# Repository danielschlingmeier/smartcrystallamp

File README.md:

# smartcrystallamp
Smart Crystal Lamp Project

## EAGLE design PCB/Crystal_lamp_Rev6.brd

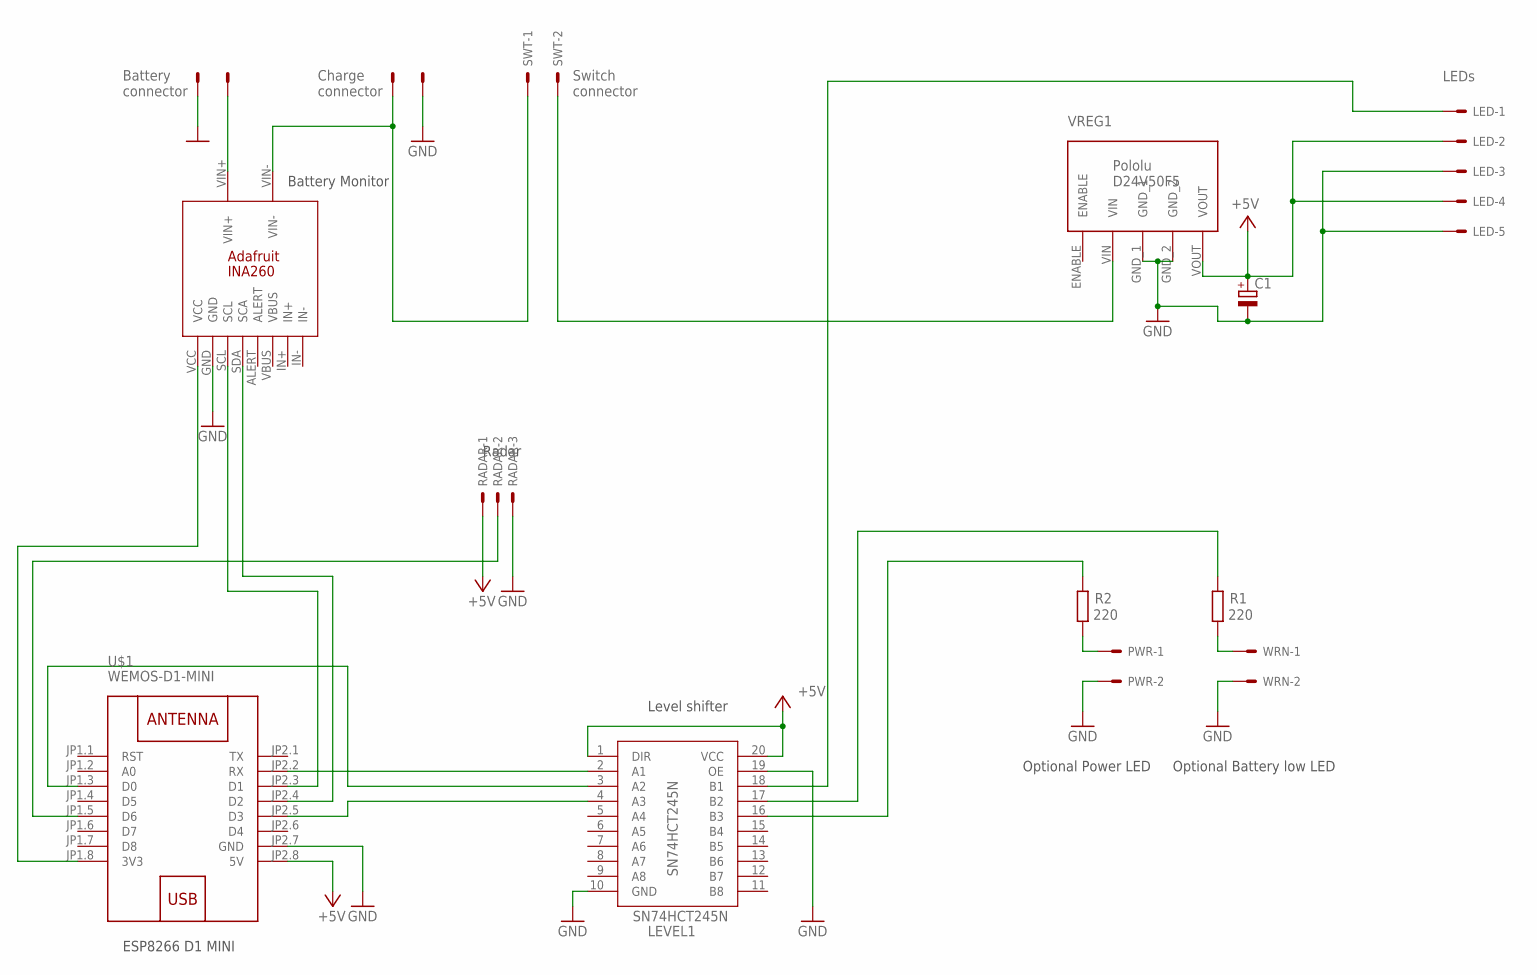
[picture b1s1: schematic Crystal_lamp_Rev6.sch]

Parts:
BAT: 22-27-2021-02; 6410-02
C1: CPOL-EUE5-10.5; E5-10,5
CRG: 22-27-2021-02; 6410-02
INA1: INA260
LED: 22-27-2051-05; 6410-05
LEVEL1: SN74HCT245N; DIL20
PWR: 22-27-2021-02; 6410-02
R1, R2: 220; 0207/10
RADAR: 22-27-2031-03; 6410-03
SWT: 22-27-2021-02; 6410-02
U$1: WEMOS-D1-MINI
VREG1: D24V50F5
WRN: 22-27-2021-02; 6410-02

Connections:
+5V: C1.+, LED.2, LED.4, LEVEL1.1 (DIR), LEVEL1.20 (VCC), RADAR.1, U$1.JP2.8 (5V), VREG1.VOUT
GND: BAT.2, C1.-, CRG.2, INA1.GND, LED.3, LED.5, LEVEL1.10 (GND), LEVEL1.19 (OE), PWR.2, RADAR.3, U$1.JP2.7 (GND), VREG1.GND_1, VREG1.GND_2, WRN.2
unnamed: LEVEL1.4 (A3), U$1.JP2.5 (D3)
unnamed: LEVEL1.3 (A2), U$1.JP1.3 (D0)
unnamed: R1.1, WRN.1
unnamed: LEVEL1.2 (A1), U$1.JP2.2 (RX)
unnamed: BAT.1, INA1.VIN+
unnamed: LED.1, LEVEL1.18 (B1)
unnamed: LEVEL1.17 (B2), R1.2
unnamed: LEVEL1.16 (B3), R2.2
unnamed: CRG.1, INA1.VIN-, SWT.1
unnamed: INA1.VCC, U$1.JP1.8 (3V3)
unnamed: PWR.1, R2.1
unnamed: RADAR.2, U$1.JP1.5 (D6)
unnamed: SWT.2, VREG1.VIN
SCL: INA1.SCL, U$1.JP2.3 (D1)
SDA: INA1.SDA (SCA), U$1.JP2.4 (D2)

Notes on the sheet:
Radar
Battery Monitor
Level shifter
ESP8266 D1 MINI
Optional Power LED
Battery connector
LEDs
Optional Battery low LED
Charge connector
Switch connector

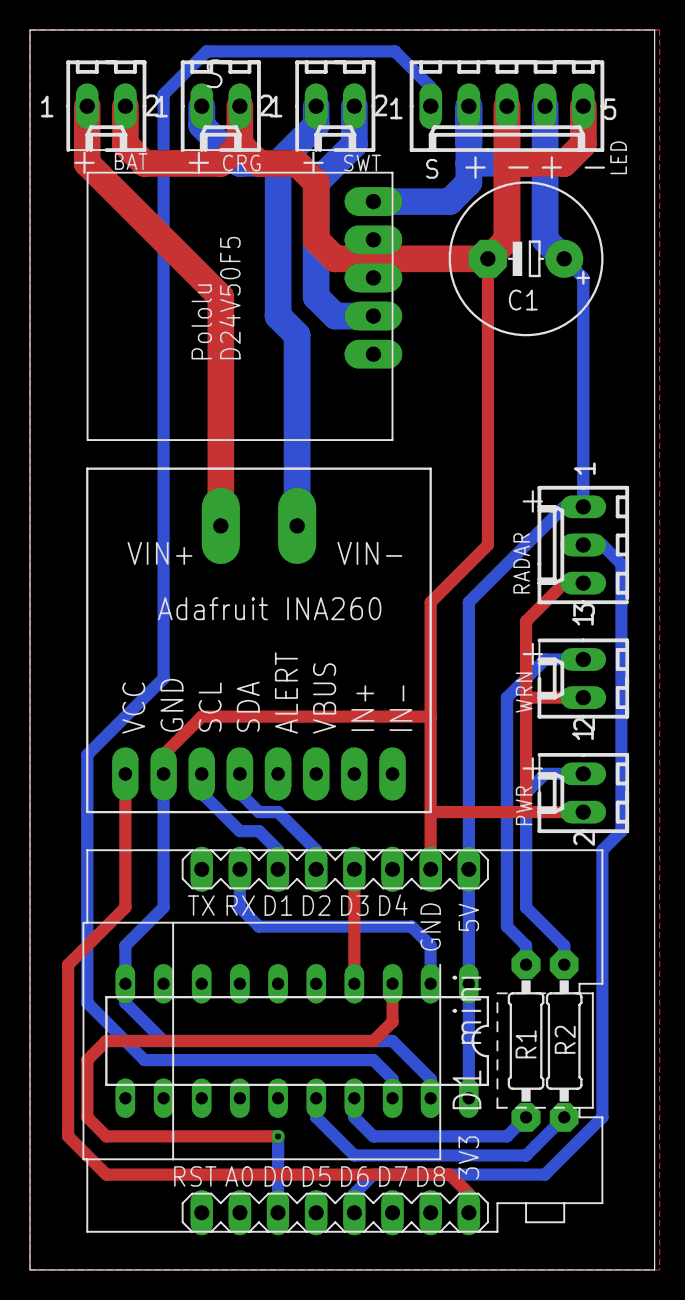
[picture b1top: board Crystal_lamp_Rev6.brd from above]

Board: 2 copper layers, 41.6 x 82.5 mm, 14 parts (0 on the bottom side), 17 nets.

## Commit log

2021-01-09 Set theme jekyll-theme-cayman
2021-01-24 STL, PCB, datasheets
    Design data, STL, PCB and component datasheets added
2021-01-31 LED switched, DHCP overwrite bug fixed
    LEDs on new PCB are switched, SW corrected
    Bug with non-accepting Lamp and Gateway IP on Wifi Page
2021-01-31 Restart botton fixed
    Little bugfix, the restart button didn't work
2021-01-31 Adding Radar Motion Effect interface to Radar.h
2021-02-14 Motion mode integrated
    Motion mode integrated
    Radar.h commented and finished
2021-02-14 Webserver cleanup

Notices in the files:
parts and their libraries:
diy-modules: Released under the Creative Commons Attribution 4.0 International License: http://creativecommons.org/licenses/by/4.0
